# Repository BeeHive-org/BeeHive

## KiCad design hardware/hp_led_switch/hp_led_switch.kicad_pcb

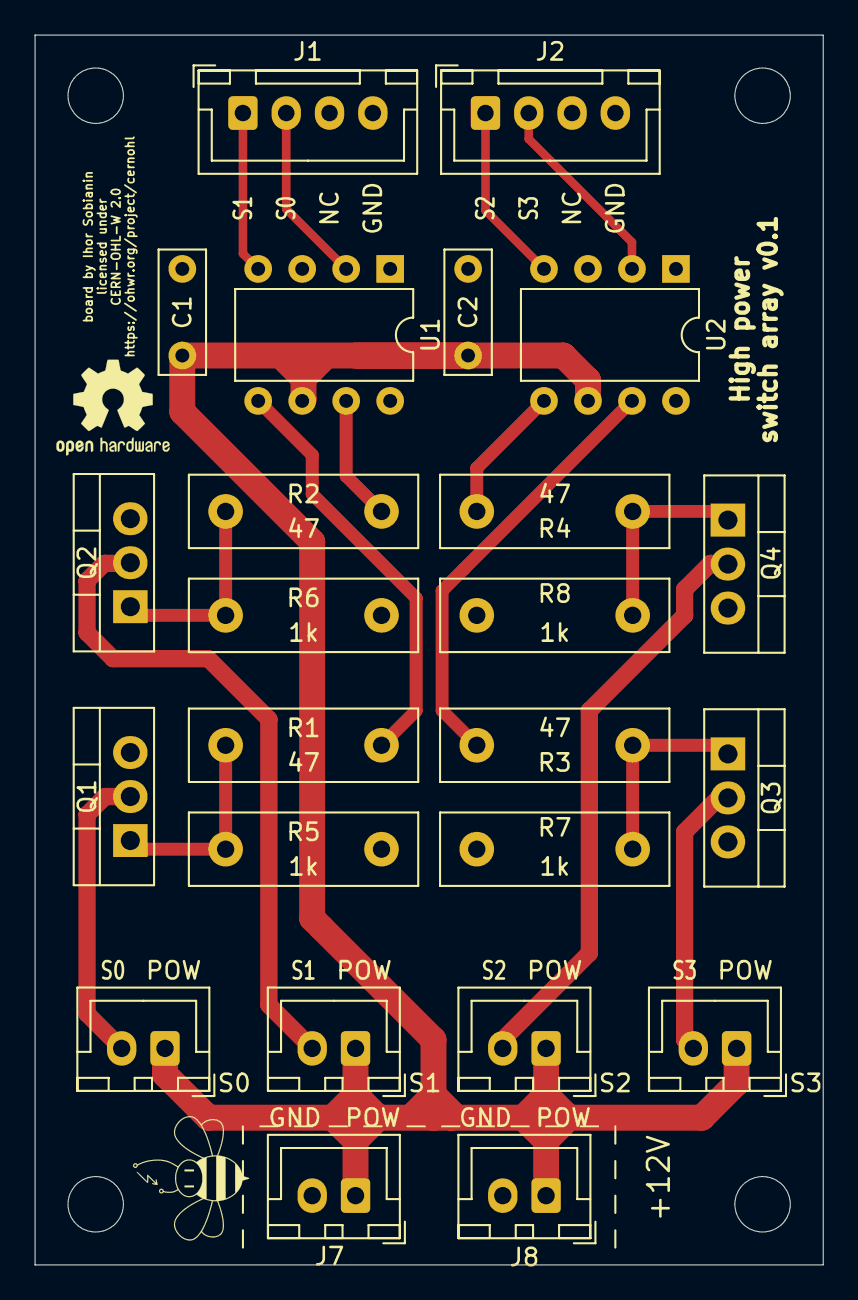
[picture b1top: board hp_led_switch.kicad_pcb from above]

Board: 2 copper layers, 45.5 x 71.0 mm, 24 parts (0 on the bottom side), 14 nets.

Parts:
C1, C2: 100nF; C_Disc_D7.0mm_W2.5mm_P5.00mm
J1, J2: Conn_01x04; JST_XH_B4B-XH-A_1x04_P2.50mm_Vertical
J3, J4, J5, J6, J7, J8: Conn_01x02; JST_XH_B2B-XH-A_1x02_P2.50mm_Vertical
Q1, Q2, Q3, Q4: IRLZ44N; TO-220-3_Vertical
R1, R2, R3, R4: 47; R_Box_L13.0mm_W4.0mm_P9.00mm
R5, R6, R7, R8: 1k; R_Box_L13.0mm_W4.0mm_P9.00mm
U1, U2: TC4427CPA; DIP-8_W7.62mm

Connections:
+12V: C1.1, C2.1, J3.1, J4.1, J5.1, J6.1, J7.1, J8.1, U1.6, U2.6
GND: C1.2, C2.2, J1.4, J2.4, J7.2, J8.2, Q1.3, Q2.3, Q3.3, Q4.3, R5.1, R6.1, R7.1, R8.1, U1.3, U2.3
unnamed: J3.2, Q1.2
unnamed: J4.2, Q2.2
unnamed: J5.2, Q4.2
unnamed: J6.2, Q3.2
unnamed: Q1.1, R1.2, R5.2
unnamed: Q2.1, R2.2, R6.2
unnamed: Q3.1, R3.2, R7.2
unnamed: Q4.1, R4.2, R8.2
unnamed: R1.1, U1.5
unnamed: R2.1, U1.7
unnamed: R3.1, U2.7
unnamed: R4.1, U2.5

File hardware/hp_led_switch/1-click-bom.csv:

References,Qty,Description,Manufacturer,MPN,Manufacturer,MPN,Manufacturer,MPN,Manufacturer,MPN,Manufacturer,MPN,Digikey,Mouser,RS,Newark,Farnell
J1;J2;,2,CONN HEADER XH TOP 4POS 2.5MM,JST,B4B-XH-A (LF)(SN),,,,,,,,,455-2249-ND,,8201551,,1516278
J3; J4; J5; J6;,4,CONN HEADER XH TOP 2POS 2.5MM,JST,B2B-XH-A (LF)(SN),,,,,,,,,455-2247-ND,,8201554P,73M9415,1516276
C1;C2;,2,100nF Capacitor Disc,Multicomp,MCFYU6104Z6,KEMET,C052C104K5R5CA,KEMET,C052K104K5X5CA,KEMET,C052T104K5X5CS,KEMET,C321C104K5R5HA,BC1101CT-ND,80C321C104K5R5HA,8523277,73M2154,2395773
Q1;Q2;Q3;Q4;,4,IRFZ24NPBF or IRFZ44NPbF footprint TO-220AB,Infineon,IRFZ44NPbF,,,,,,,,,IRFZ44NPBF-ND,942IRFZ44NPBF,5409777,,1544411
U1;U2,2,TC4427 footprint PDIP-8,Microchip,TC4427,Microchip,TC4427CPA,,,,,,,TC4427CPA-ND,579TC4427CPA,2070180,,9762639
R1;R2;R3;R4,4,Resistor 47 ohm 250mW through-hole,TE Connectivity,ROX1SJ47R,,,,,,,,,A131472CT-ND,279ROX1S47R,2140964,,1738569
R5;R6;R7;R8,4,Resistor 1k ohm 250mW through-hole,TE Connectivity,CFR16J1K0,,,,,,,,,A104669CT-ND,279216239273,1251150,,2329486
cables,6,"JUMPER SXH-001T-P0.6 X2 10""""",JST,ASXHSXH22K254,,,,,,,,,455-4223-ND,,,,
connectors 2pin,8,CONN HOUSING 2.5MM 2POS,JST,XHP-2,,,,,,,,,455-2266-ND,,8201611,,1516264
connectors 4pin,4,CONN HOUSING 2.5MM 4POS,JST,XHP-4,,,,,,,,,455-2267-ND,,8201618,,1516266

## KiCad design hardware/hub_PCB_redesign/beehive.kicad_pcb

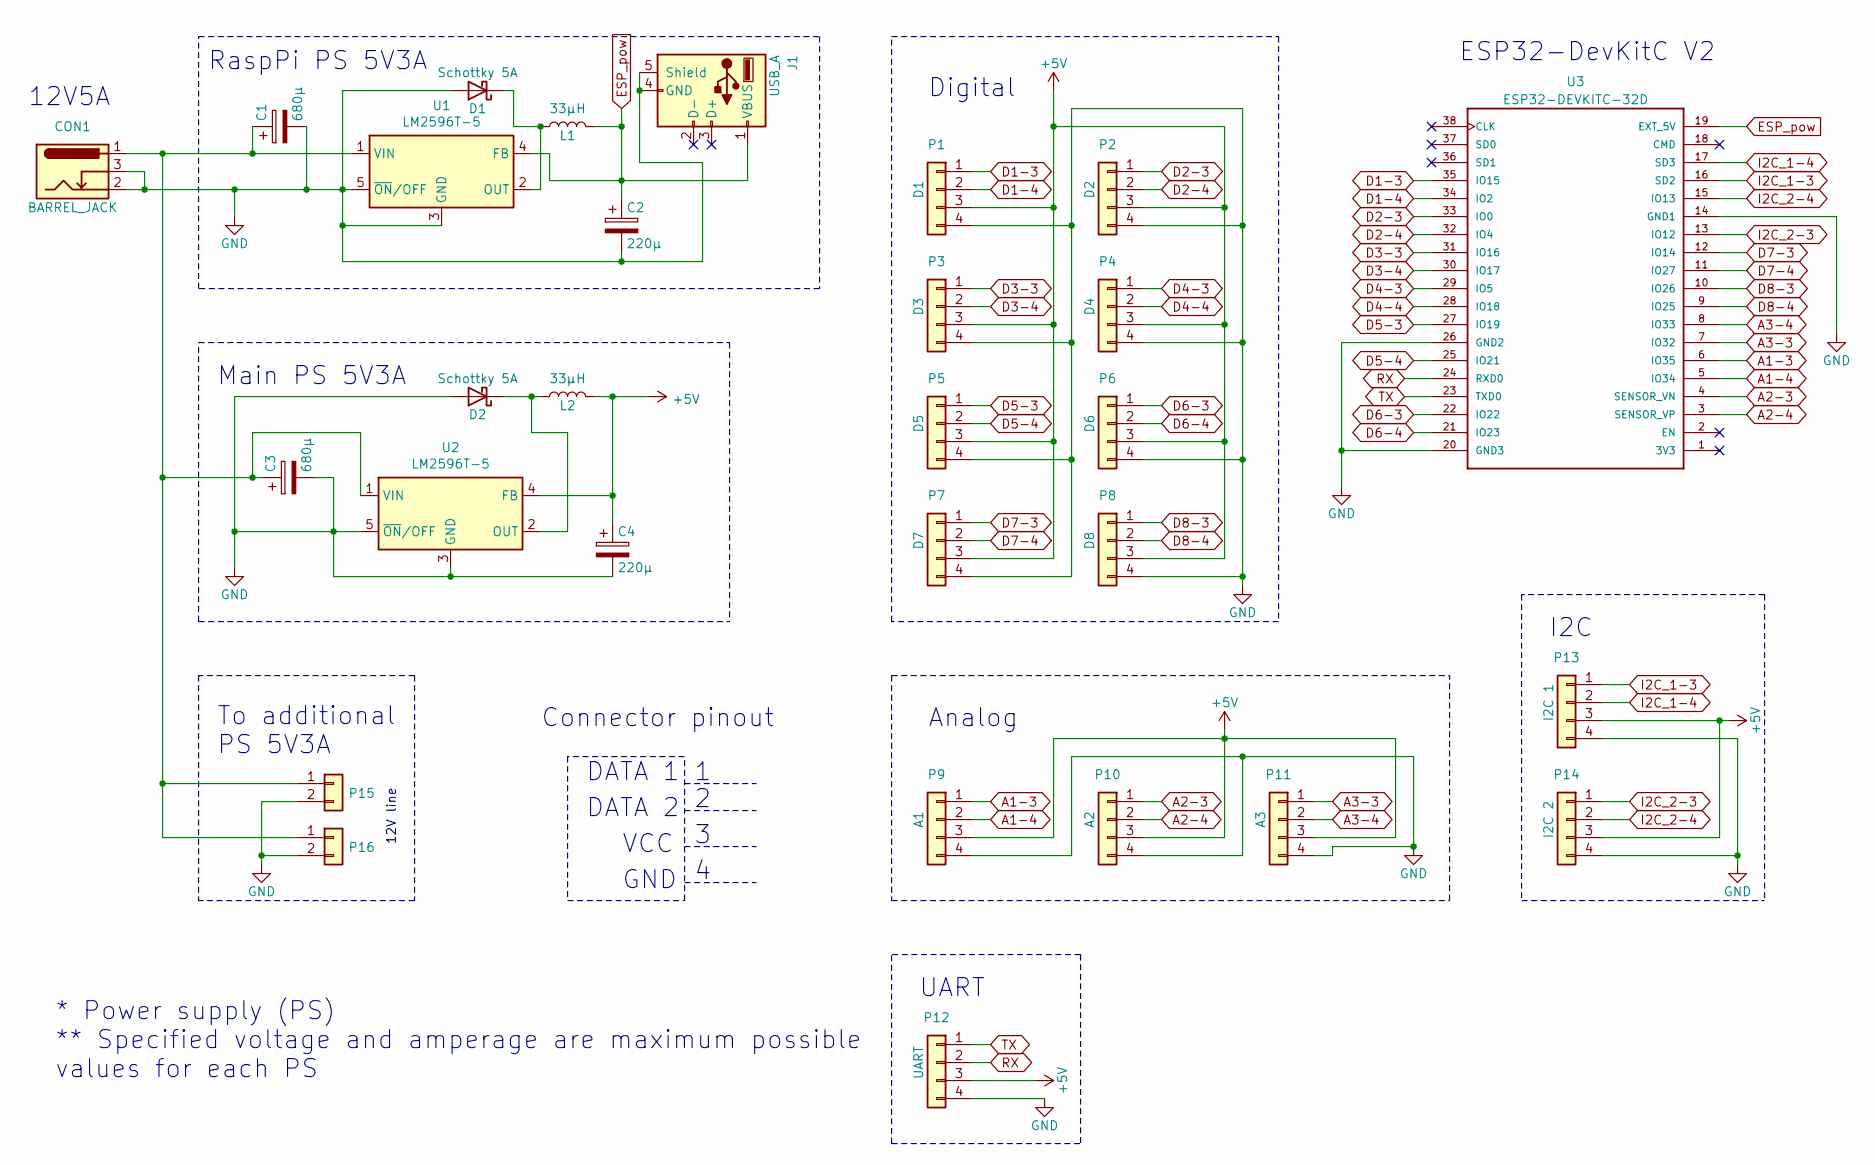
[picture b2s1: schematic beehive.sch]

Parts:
C1, C3: 680µ; C_Radial_D10_L21_P5
C2, C4: 220µ; C_Radial_D8_L13_P3.8
CON1: BARREL_JACK; BarrelJack_Horizontal
D1, D2: Schottky 5A; Diode_DO-201AD_Horizontal_RM15
J1: USB_A; USB_A_Vertical
L1, L2: 33µH; Neosid_Inductor_MA-Bs75
P1: D1; JST_XH_B04B-XH-A_04x2.50mm_Straight
P2: D2; JST_XH_B04B-XH-A_04x2.50mm_Straight
P3: D3; JST_XH_B04B-XH-A_04x2.50mm_Straight
P4: D4; JST_XH_B04B-XH-A_04x2.50mm_Straight
P5: D5; JST_XH_B04B-XH-A_04x2.50mm_Straight
P6: D6; JST_XH_B04B-XH-A_04x2.50mm_Straight
P7: D7; JST_XH_B04B-XH-A_04x2.50mm_Straight
P8: D8; JST_XH_B04B-XH-A_04x2.50mm_Straight
P9: A1; JST_XH_B04B-XH-A_04x2.50mm_Straight
P10: A2; JST_XH_B04B-XH-A_04x2.50mm_Straight
P11: A3; JST_XH_B04B-XH-A_04x2.50mm_Straight
P12: UART; JST_XH_B04B-XH-A_04x2.50mm_Straight
P13: I2C 1; JST_XH_B04B-XH-A_04x2.50mm_Straight
P14: I2C 2; JST_XH_B04B-XH-A_04x2.50mm_Straight
P15, P16: Conn_01x02; JST_XH_B2B-XH-A_1x02_P2.50mm_Vertical
U1, U2: LM2596T-5; TO-220-5_P3.4x3.7mm_StaggerOdd_Lead3.8mm_Vertical
U3: ESP32-DEVKITC-32D; MODULE_ESP32-DEVKITC-32D

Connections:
+5V: C4.1, L2.2, P1.3, P2.3, P3.3, P4.3, P5.3, P6.3, P7.3, P8.3, P9.3, P10.3, P11.3, P12.3, P13.3, P14.3, U2.4 (FB)
A1-3: P9.1, U3.6 (IO35)
A1-4: P9.2, U3.5 (IO34)
A2-3: P10.1, U3.4 (SENSOR_VN)
A2-4: P10.2, U3.3 (SENSOR_VP)
A3-3: P11.1, U3.7 (IO32)
A3-4: P11.2, U3.8 (IO33)
D1-3: P1.1, U3.35 (IO15)
D1-4: P1.2, U3.34 (IO2)
D2-3: P2.1, U3.33 (IO0)
D2-4: P2.2, U3.32 (IO4)
D3-3: P3.1, U3.31 (IO16)
D3-4: P3.2, U3.30 (IO17)
D4-3: P4.1, U3.29 (IO5)
D4-4: P4.2, U3.28 (IO18)
D5-3: P5.1, U3.27 (IO19)
D5-4: P5.2, U3.25 (IO21)
D6-3: P6.1, U3.22 (IO22)
D6-4: P6.2, U3.21 (IO23)
D7-3: P7.1, U3.12 (IO14)
D7-4: P7.2, U3.11 (IO27)
D8-3: P8.1, U3.10 (IO26)
D8-4: P8.2, U3.9 (IO25)
ESP_pow: C2.1, J1.1 (VBUS), L1.2, U1.4 (FB), U3.19 (EXT_5V)
GND: C1.2, C2.2, C3.2, C4.2, CON1.2, CON1.3, D1.2 (A), D2.2 (A), J1.4 (GND), J1.5 (Shield), P1.4, P2.4, P3.4, P4.4, P5.4, P6.4, P7.4, P8.4, P9.4, P10.4, P11.4, P12.4, P13.4, P14.4, P15.2, P16.2, U1.3 (GND), U1.5 (~ON~/OFF), U2.3 (GND), U2.5 (~ON~/OFF), U3.14 (GND1), U3.20 (GND3), U3.26 (GND2)
I2C_1-3: P13.1, U3.16 (SD2)
I2C_1-4: P13.2, U3.17 (SD3)
I2C_2-3: P14.1, U3.13 (IO12)
I2C_2-4: P14.2, U3.15 (IO13)
unnamed: C1.1, C3.1, CON1.1, P15.1, P16.1, U1.1 (VIN), U2.1 (VIN)
unnamed: D1.1 (K), L1.1, U1.2 (OUT)
unnamed: D2.1 (K), L2.1, U2.2 (OUT)
RX: P12.2, U3.24 (RXD0)
TX: P12.1, U3.23 (TXD0)

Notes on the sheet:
I2C
Main PS 5V3A
RaspPi PS 5V3A
ESP32-DevKitC V2
UART
12V5A
Connector pinout
Analog
Digital
GND
VCC
DATA 1
DATA 2
* Power supply (PS) ** Specified voltage and amperage are maximum possible values for each PS
To additional PS 5V3A
12V line

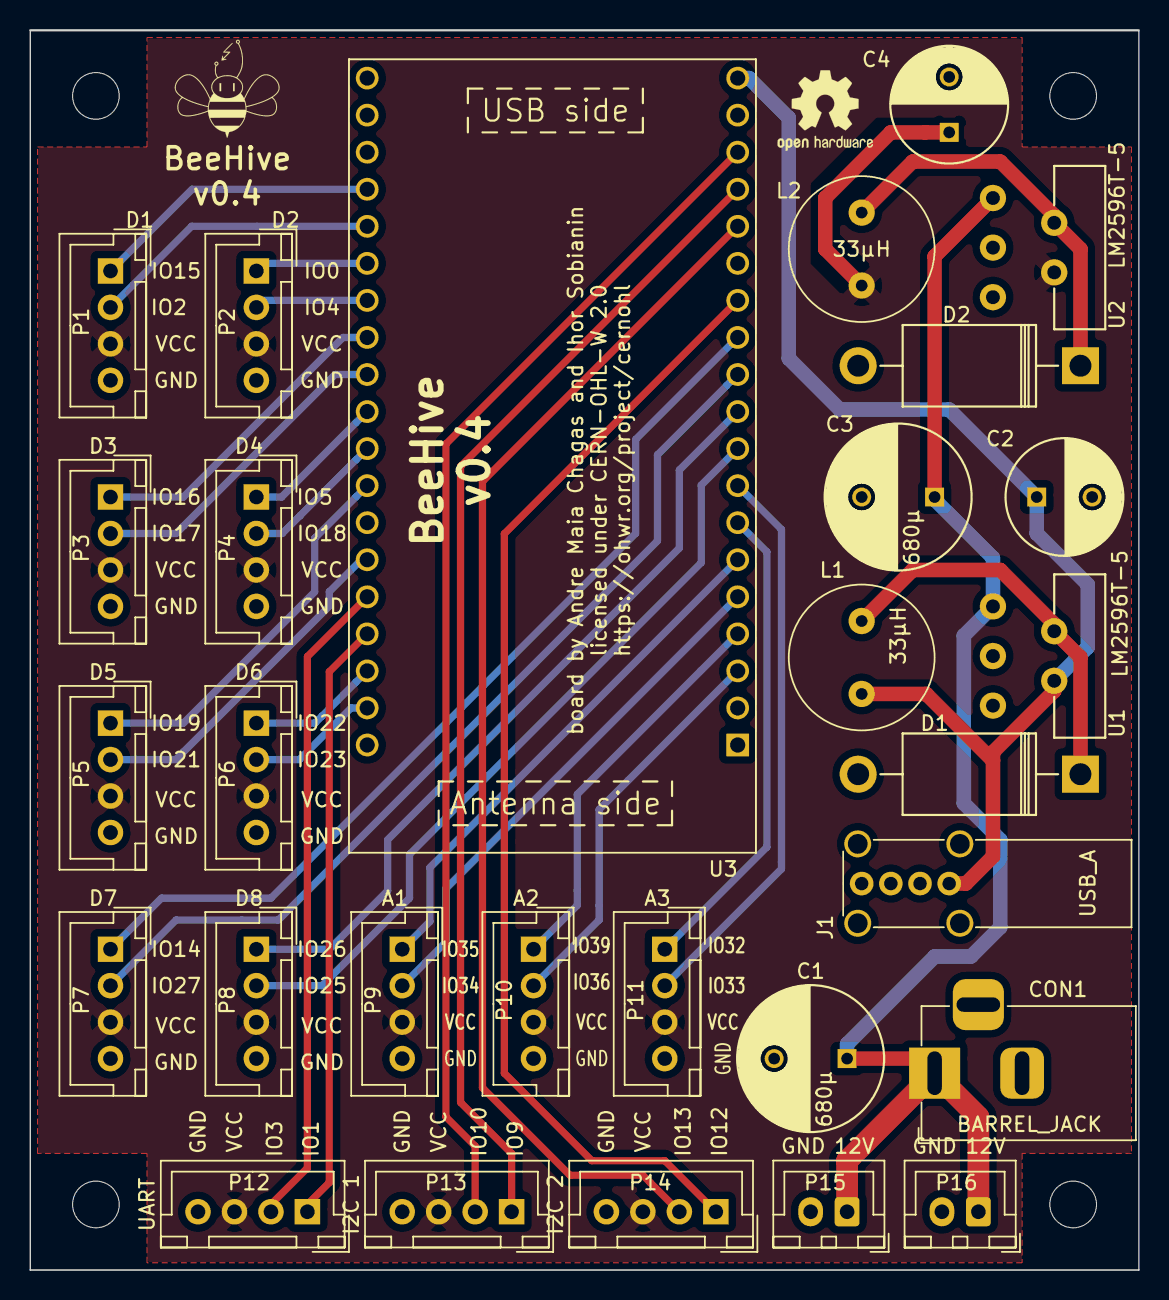
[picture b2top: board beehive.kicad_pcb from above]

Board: 2 copper layers, 76.0 x 85.0 mm, 30 parts (0 on the bottom side), 34 nets.

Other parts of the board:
 : OSHW-Logo2_7.3x6mm_SilkScreen

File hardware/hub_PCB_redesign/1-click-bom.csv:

References,Qty,Description,Manufacturer,MPN,Manufacturer,MPN,Manufacturer,MPN,Manufacturer,MPN,Manufacturer,MPN,Digikey,Mouser,RS,Newark,Farnell
U1; U2,2,LM2596 5v,ITO-220,Texas Instruments,Texas Instruments,LM2596T-5.0/NOPB,,,,,,,LM2596T-5.0/NOPB-ND,926LM2596T5.0/NOPB,5333743,,3008166
U3;,1,ESP32-DevKitC-VIB,,,,,,,,,,,,,,,
P1;P2;P3;P4;P5;P6;P7;P8;P9;P10;P11;P12;P13;P14;P15;,15,CONN HEADER XH TOP 4POS 2.5MM,JST,B4B-XH-A (LF)(SN),,,,,,,,,455-2249-ND,,8201551,,1516278
L1; L2;,2,INDUCTOR 33µH Neosid MA-Bs75,Bourns,RLB0914-330KL,Bourns,RLB9012-330KL,,,,,,,RLB9012-330KL-ND,652RLB0914330KL,8118853,,2309242
J1;,1,USB A Vertical,FCI,73725-0110BLF,Molex,48204-0001,,,,,,,609-1041-ND,649737250110BLF,7710048,,2782046
D1; D2;,2,Diode Schottky 5A DO-201AD,Vishay,1N5822-E3/73,Zetex,SB5100-T,,,,,,,1N5822-E3/73GICT-ND,6251N5822E3/73,7514843,,1336553
CON1;,1,2.1mm socket,Cliff,FC68148 DC10A,Lumberg,NEB 21 R,Cliff,FC68148,Gravitech,CON-SOCJ-2155,Parallax,452-00007,SC1313-ND,992CONSOCJ2155,5051609,,1217037
C1; C3;,2,680µF Capacitor,Rubycon,16ZL680MEFC10X16,Panasonic,EEU-FC1A681,Panasonic,EEU-FP1E681,,,,,1189-3978-ND,667EEUFP1E681,1793151,,2911616
C2; C4;,2,CAP ALUM 220UF 20% 25V RADIAL,Panasonic,EEU-FM1E221,Panasonic,ECA-1CM221B,Panasonic,ECE-A0GKS221,Panasonic,EEU-EB1A221S,,,P13456-ND,667ECA1CM221B,7472036,,9451099

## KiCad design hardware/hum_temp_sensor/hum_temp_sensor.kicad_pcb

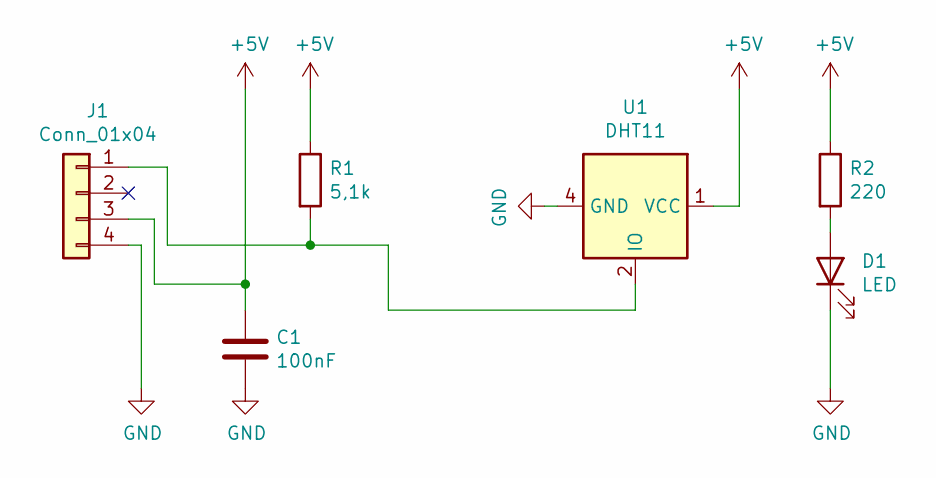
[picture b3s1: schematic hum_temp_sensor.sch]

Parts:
C1: 100nF; C_Disc_D7.0mm_W2.5mm_P5.00mm
D1: LED; LED_D3.0mm
J1: Conn_01x04; JST_XH_B4B-XH-A_1x04_P2.50mm_Vertical
R1: 5,1k; R_Box_L13.0mm_W4.0mm_P9.00mm
R2: 220; R_Box_L13.0mm_W4.0mm_P9.00mm
U1: DHT11; Aosong_DHT11_5.5x12.0_P2.54mm

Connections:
+5V: C1.1, J1.3, R1.1, R2.1, U1.1 (VCC)
GND: C1.2, D1.1 (K), J1.4, U1.4 (GND)
unnamed: D1.2 (A), R2.2
unnamed: J1.1, R1.2, U1.2 (IO)

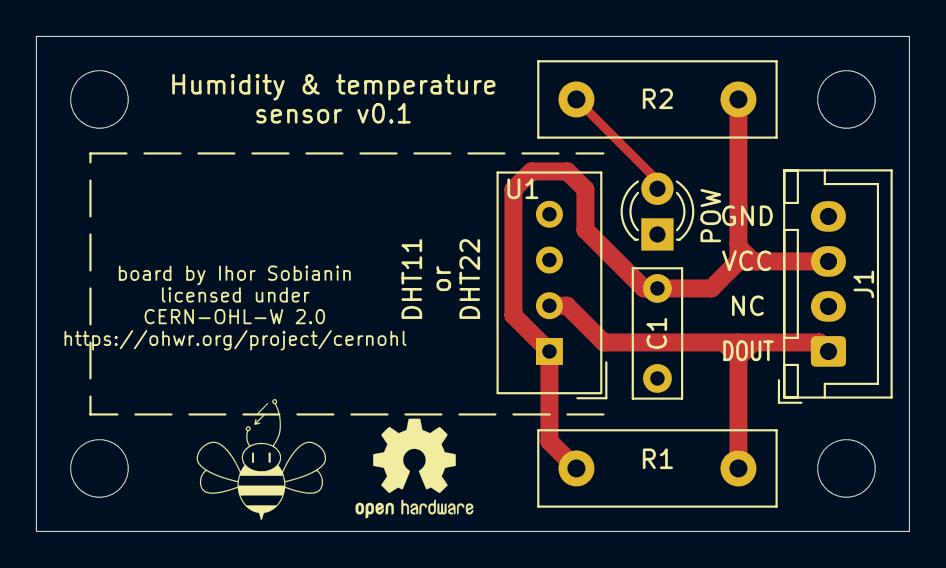
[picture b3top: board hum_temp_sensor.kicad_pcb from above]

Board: 2 copper layers, 48.5 x 27.5 mm, 6 parts (0 on the bottom side), 4 nets.

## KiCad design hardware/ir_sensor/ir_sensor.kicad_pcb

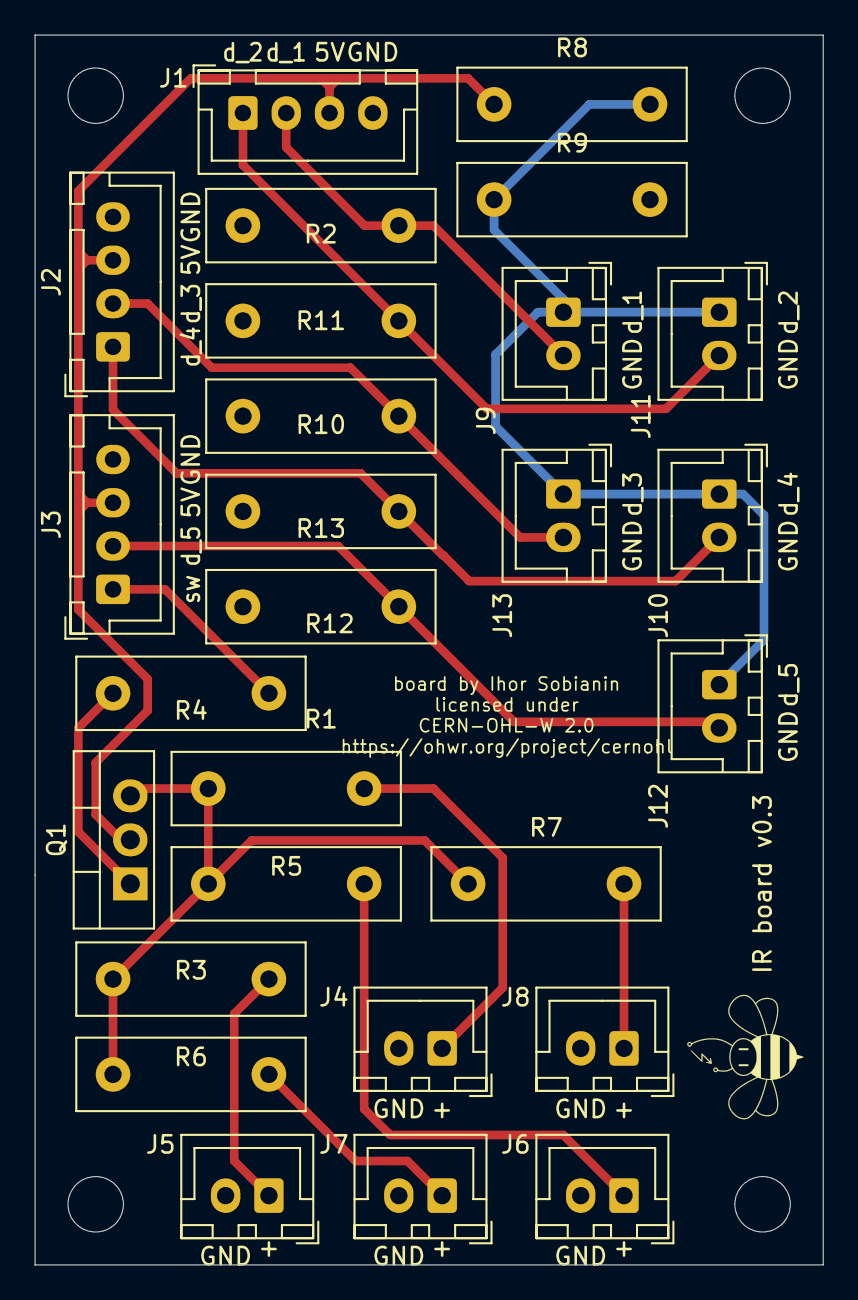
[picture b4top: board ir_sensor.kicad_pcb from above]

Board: 2 copper layers, 45.5 x 71.0 mm, 27 parts (0 on the bottom side), 16 nets.

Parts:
J1, J2, J3: Conn_01x04; JST_XH_B4B-XH-A_1x04_P2.50mm_Vertical
J4, J5, J6, J7, J8, J9, J10, J11, J12, J13: Conn_01x02; JST_XH_B2B-XH-A_1x02_P2.50mm_Vertical
Q1: IRFZ24NPBF; TO-220-3_Vertical
R1, R3, R4, R5, R6, R7: 47; R_Box_L13.0mm_W4.0mm_P9.00mm
R2, R10, R11, R12, R13: 10k; R_Box_L13.0mm_W4.0mm_P9.00mm
R8: 560; R_Box_L13.0mm_W4.0mm_P9.00mm
R9: 1k; R_Box_L13.0mm_W4.0mm_P9.00mm

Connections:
+3V3: J9.1, J10.1, J11.1, J12.1, J13.1, R8.2, R9.1
+5V: J1.3, J2.3, J3.3, Q1.2, R8.1
GND: J1.4, J2.4, J3.4, J4.2, J5.2, J6.2, J7.2, J8.2, R2.2, R9.2, R10.2, R11.2, R12.2, R13.2
unnamed: J4.1, R1.2
unnamed: J5.1, R3.2
unnamed: J6.1, R5.2
unnamed: J7.1, R6.2
unnamed: J8.1, R7.2
unnamed: Q1.1, R4.2
Vdrive: Q1.3, R1.1, R3.1, R5.1, R6.1, R7.1
d_1: J1.2, J9.2, R2.1
d_2: J1.1, J11.2, R11.1
d_3: J2.2, J13.2, R10.1
d_4: J2.1, J10.2, R13.1
d_5: J3.2, J12.2, R12.1
sw_led: J3.1, R4.1

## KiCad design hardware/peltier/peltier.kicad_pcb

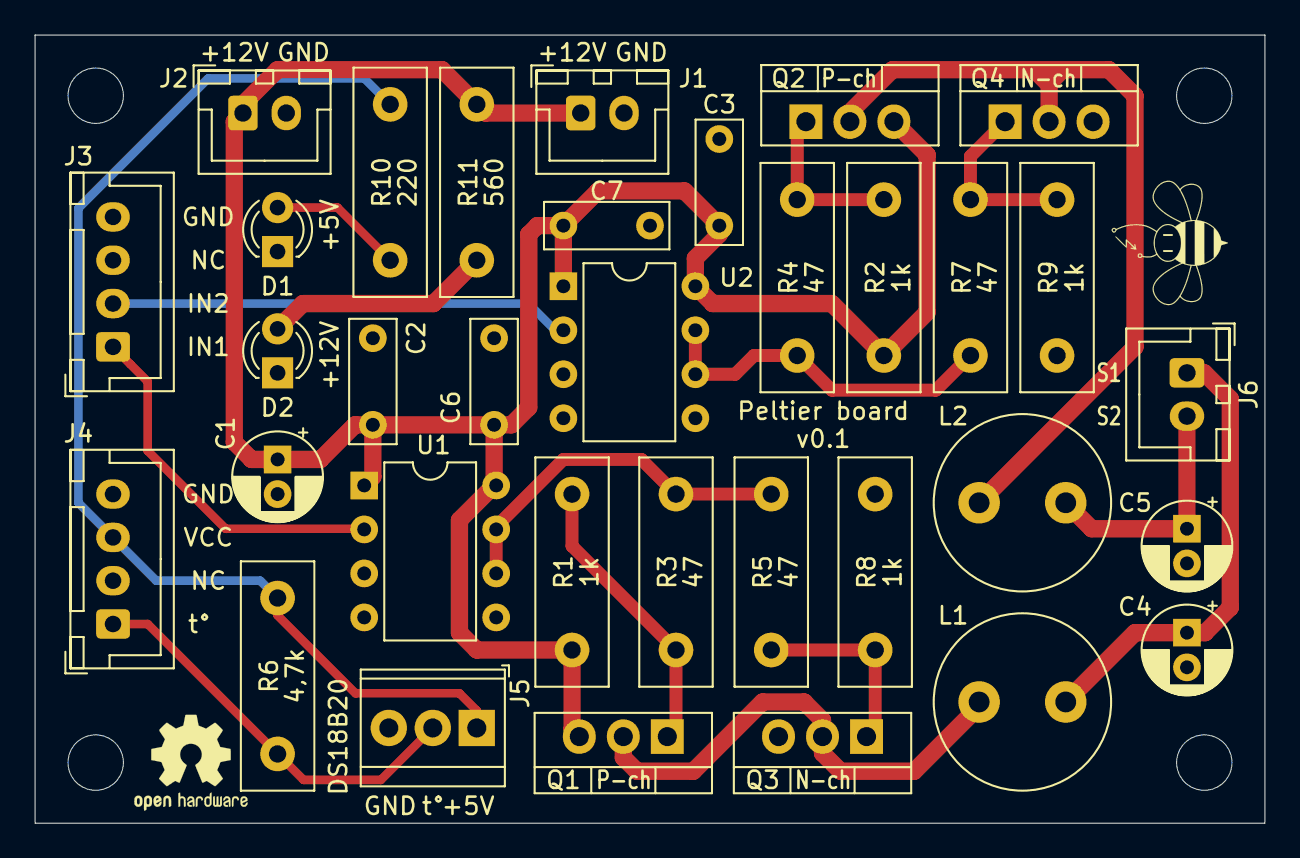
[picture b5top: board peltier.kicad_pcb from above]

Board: 2 copper layers, 71.0 x 45.5 mm, 34 parts (0 on the bottom side), 18 nets.

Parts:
C1, C4, C5: 22u; CP_Radial_D5.0mm_P2.00mm
C2, C3, C6, C7: 100nF; C_Disc_D7.0mm_W2.5mm_P5.00mm
D1, D2: LED; LED_D3.0mm
J1, J2, J6: Conn_01x02; JST_XH_B2B-XH-A_1x02_P2.50mm_Vertical
J3, J4: Conn_01x04; JST_XH_B4B-XH-A_1x04_P2.50mm_Vertical
J5: Conn_01x03; TerminalBlock_TE_282834-3_1x03_P2.54mm_Horizontal
L1, L2: 33u; L_Radial_D10.0mm_P5.00mm_Neosid_SD12_style3
Q1, Q2: IRF9Z34NPBF; TO-220-3_Vertical
Q3, Q4: IRFZ24NPBF; TO-220-3_Vertical
R1, R2, R8, R9: 1k; R_Box_L13.0mm_W4.0mm_P9.00mm
R3, R4, R5, R7: 47; R_Box_L13.0mm_W4.0mm_P9.00mm
R6: 4,7k; R_Box_L13.0mm_W4.0mm_P9.00mm
R10: 220; R_Box_L13.0mm_W4.0mm_P9.00mm
R11: 560; R_Box_L13.0mm_W4.0mm_P9.00mm
U1, U2: TC4420CPA; DIP-8_W7.62mm

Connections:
+5V: J4.3, J5.1, R6.2, R10.1
+12V: C1.1, C2.1, C3.1, C6.1, C7.1, J1.1, J2.1, Q1.3, Q2.3, R1.2, R2.2, R11.1, U1.1, U1.8, U2.1, U2.8
GND: C1.2, C2.2, C3.2, C4.2, C5.2, C6.2, C7.2, D1.1, D2.1, J1.2, J2.2, J3.4, J4.4, J5.3, Q3.3, Q4.3, R8.1, R9.1, U1.4, U1.5, U2.4, U2.5
IN1: J3.1, U1.2
IN2: J3.2, U2.2
unnamed: C4.1, J6.1, L1.2
unnamed: C5.1, J6.2, L2.2
unnamed: D1.2, R10.2
unnamed: D2.2, R11.2
unnamed: L1.1, Q1.2, Q3.2
unnamed: L2.1, Q2.2, Q4.2
unnamed: Q1.1, R1.1, R3.2
unnamed: Q2.1, R2.1, R4.2
unnamed: Q3.1, R5.2, R8.2
unnamed: Q4.1, R7.2, R9.2
unnamed: R3.1, R5.1, U1.6, U1.7
unnamed: R4.1, R7.1, U2.6, U2.7
t: J4.1, J5.2, R6.1

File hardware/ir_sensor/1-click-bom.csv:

References,Qty,Description,Manufacturer,MPN,Manufacturer,MPN,Manufacturer,MPN,Manufacturer,MPN,Manufacturer,MPN,Manufacturer,MPN,Manufacturer,MPN,Manufacturer,MPN,Manufacturer,MPN,Digikey,Mouser,RS,Newark,Farnell
U1;U2,2,TC4420 footprint PDIP-8,Microchip,TC4420CPA,Microchip,TC4420EPA,,,,,,,,,,,,,,,TC4420EPA-ND,579TC4420EPA,6811124,,9762566
Q1;Q2,4,IRF9Z34NPBF or IRF4905PbF footprint TO-220AB,Infineon,IRF4905PBF,Infineon,IRF9Z34NPBF,,,,,,,,,,,,,,,IRF9Z34NPBF-ND,942IRF9Z34NPBF,5409799,,8648689
Q3;Q4,4,IRFZ24NPBF or IRFZ44NPbF footprint TO-220AB,Infineon,IRFZ44NPbF,Infineon,IRFZ44NPBF,,,,,,,,,,,,,,,IRFZ44NPBF-ND,942IRFZ44NPBF,5409777,,1544411
R3;R4;R5;R7,4,Resistor 47 ohm 250mW through-hole,TE Connectivity,LR1F47R,TE Connectivity,ROX1SJ47R,,,,,,,,,,,,,,,A131472CT-ND,279LR1F47R,148174,,1738569
R1;R2;R8;R9,4,Resistor 1k ohm 250mW through-hole,TE Connectivity,CFR16J1K0,TE Connectivity,ROX2SJ1K0,,,,,,,,,,,,,,,A104669CT-ND,279ROX2SJ1K0,2141951,,1738638
R10;,1,Resistor 220 ohm 250mW through-hole,Yageo,MFR-25FBF52-220R,TE Connectivity,LR1F220R,,,,,,,,,,,,,,,MFR-25FBF52-220R-ND,279LR1F220R,148348,,2330065
R11;,1,Resistor 560 ohm 250mW through-hole,TE Connectivity,CFR25J560R,KOA Speer,CF1/2CT52R561J,,,,,,,,,,,,,,,2019-CF1/2CT52R561JCT-ND,279CFR25J560R,131227,,2329690
C1;C2;C6;C7,4,100nF Capacitor Disc,Multicomp,MCFYU6104Z6,KEMET,C052C104K5R5CA,KEMET,C052K104K5X5CA,KEMET,C052T104K5X5CS,KEMET,C321C104K5R5HA,KEMET,CK05BX104K,Vishay,K104K15X7RF5TH5,Vishay,K104Z15Y5VF5TL2,Multicomp,MC0805B104K500A5.08MM,BC1101CT-ND,594K104K15X7RF5TH5,8523277,73M2154,2395773
C3;C4;C5,3,22uF CP_Radial_D5.0mm_P2.00mm,Panasonic,ECA-1HM220,,,,,,,,,,,,,,,,,P5179-ND,667ECA1HM220,2286880,,9693777
L1; L2;,2,INDUCTOR 33�H Neosid MA-Bs75,Bourns,RLB0914-330KL,Bourns,RLB9012-330KL,,,,,,,,,,,,,,,RLB9012-330KL-ND,652RLB9012330KL,8118853,61J7916,2309242
J1;J2,2,CONN HEADER XH TOP 2POS 2.5MM,JST,B2B-XH-A (LF)(SN),JST,B2B-XH-A(LF)(SN),,,,,,,,,,,,,,,455-2247-ND,,8201554,73M9415,1516276
J3;,1,CONN HEADER XH TOP 4POS 2.5MM,JST,B4B-XH-A (LF)(SN),JST,B4B-XH-A(LF)(SN),,,,,,,,,,,,,,,455-2249-ND,,8201551,,1516278
J6;,1,Terminal block 5mm,RS Pro,494-8906,TE Connectivity,282837-2,RS Pro,4948906,,,,,,,,,,,,,A113320-ND,5712828372,7100100,,1784860
D1;D2,2,3mm LED any colour,Bivar Inc,ELM 5-065,Bivar,ELM 5-065,,,,,,,,,,,,,,,492-2284-ND,749ELM5065,,,
cables,16,"JUMPER SXH-001T-P0.6 X2 10""""",JST,ASXHSXH22K254,,,,,,,,,455-4223-ND,,,,,,,,,,,,
connectors 2pin,4,CONN HOUSING 2.5MM 2POS,JST,XHP-2,,,,,,,,,455-2266-ND,,8201611,,1516264,,,,,,,,
connectors 4pin,6,CONN HOUSING 2.5MM 4POS,JST,XHP-4,,,,,,,,,455-2267-ND,,8201618,,1516266,,,,,,,,

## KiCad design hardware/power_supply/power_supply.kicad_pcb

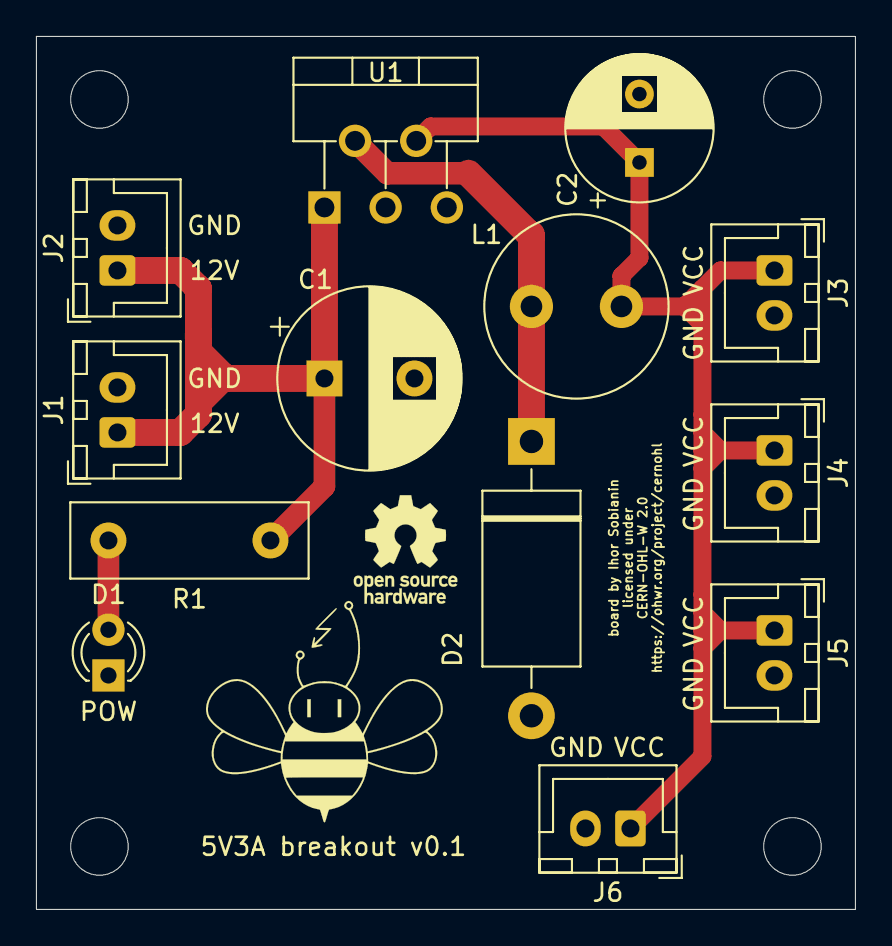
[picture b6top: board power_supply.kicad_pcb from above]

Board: 2 copper layers, 45.5 x 48.5 mm, 13 parts (0 on the bottom side), 5 nets.

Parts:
C1: 680µ; CP_Radial_D10.0mm_P5.00mm
C2: 220µ; CP_Radial_D8.0mm_P3.80mm
D1: LED; LED_D3.0mm
D2: D_Schottky; D_DO-201_P15.24mm_Horizontal
J1, J2, J3, J4, J5, J6: Conn_01x02; JST_XH_B2B-XH-A_1x02_P2.50mm_Vertical
L1: 33µH; L_Radial_D10.0mm_P5.00mm_Neosid_SD12_style3
R1: 560; R_Box_L13.0mm_W4.0mm_P9.00mm
U1: LM2596S-5; TO-220-5_P3.4x3.7mm_StaggerOdd_Lead3.8mm_Vertical

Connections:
GND: C1.2, C2.2, D1.1, D2.2, J1.2, J2.2, J3.2, J4.2, J5.2, J6.2, U1.3, U1.5
unnamed: C1.1, J1.1, J2.1, R1.1, U1.1
unnamed: C2.1, J3.1, J4.1, J5.1, J6.1, L1.2, U1.4
unnamed: D1.2, R1.2
unnamed: D2.1, L1.1, U1.2

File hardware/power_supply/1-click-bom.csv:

References,Qty,Description,Manufacturer,MPN,Manufacturer_1,MPN_2,Manufacturer_3,MPN_4,Manufacturer_5,MPN_6,Manufacturer_7,MPN_8,Digikey,Mouser,RS,Newark,Farnell
U1;,2,LM2596 5v,ITO-220,Texas Instruments,Texas Instruments,LM2596T-5.0/NOPB,,,,,,,LM2596T-5.0/NOPB-ND,926LM2596T5.0/NOPB,5333743,97K3256,1150103
J1;,1,CONN HEADER XH TOP 4POS 2.5MM,JST,B4B-XH-A (LF)(SN) ,,,,,,,,,455-2249-ND ,,820-1551,,1516278
J2; J3;,2,CONN HEADER XH TOP 2POS 2.5MM,JST,B2B-XH-A (LF)(SN),,,,,,,,,455-2247-ND,,8201554P,73M9415,1516276
L1; ,1,INDUCTOR 33µH Neosid MA-Bs75,Bourns,RLB0914-330KL,,,,,,,,,RLB0914-330KL-ND,652RLB0914330KL,8118853,61J7916,2309242
D1; ,1,Diode Schottky 5A DO-201AD,Vishay,1N5822-E3/73,Zetex,SB5100-T,,,,,,,1N5822-E3/73GICT-ND,6251N5822E3/73,751-4843,17T8202,1336553
C1;,1,680µF Capacitor,Rubycon,16ZL680MEFC10X16,Panasonic,EEU-FC1A681,Panasonic,EEU-FP1E681 ,,,,,1189-3978-ND,667-EEU-FP1E681 ,7037258,31M6417,1144691
C2; ,1,CAP ALUM 220UF 20% 25V RADIAL,Panasonic, EEU-FM1E221 ,Panasonic,ECA-1CM221B,Panasonic,ECE-A0GKS221,Panasonic,EEU-EB1A221S,,,P12383-ND,667ECA1CM221B,7472036,70K9673,9451099

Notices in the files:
hardware/hp_led_switch/hp_led_switch.kicad_pcb:
licensed under
CERN-OHL-W 2.0
hardware/hub_PCB_redesign/beehive.kicad_pcb:
licensed under CERN-OHL-W 2.0
